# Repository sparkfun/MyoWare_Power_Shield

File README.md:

MyoWare™ Power Shield
========================================

[*MyoWare™ Power Shield (DEV-13684)*](https://www.sparkfun.com/products/13684)

The MyoWare™ Power Shield is designed to pair with the MyoWare™ Muscle Sensor.  It provides power to the muscle sensor in the form of 2 x 20mm coin cells ([CR2032](https://www.sparkfun.com/products/338), [CR2025](https://www.sparkfun.com/products/11928), LR2032, etc).

Repository Contents
-------------------

* **/Hardware** - Eagle design files (.brd, .sch)
* **/Production** - Production panel files (.brd)

Documentation
--------------
* **[Hookup Guide](https://learn.sparkfun.com/tutorials/myoware-muscle-sensor-kit)** - Basic hookup guide for the MyoWare™ Power Shield.

Product Versions
----------------
* [v1.0](https://www.sparkfun.com/products/13684)- MyoWare™ Power Shield

License Information
-------------------

This product is _**open source**_!

Please review the LICENSE.md file for license information.

If you have any questions or concerns on licensing, please contact techsupport@sparkfun.com.

Distributed as-is; no warranty is given.

- Your friends at SparkFun.

Designed by Brian E. Kaminski of Advancer Technologies

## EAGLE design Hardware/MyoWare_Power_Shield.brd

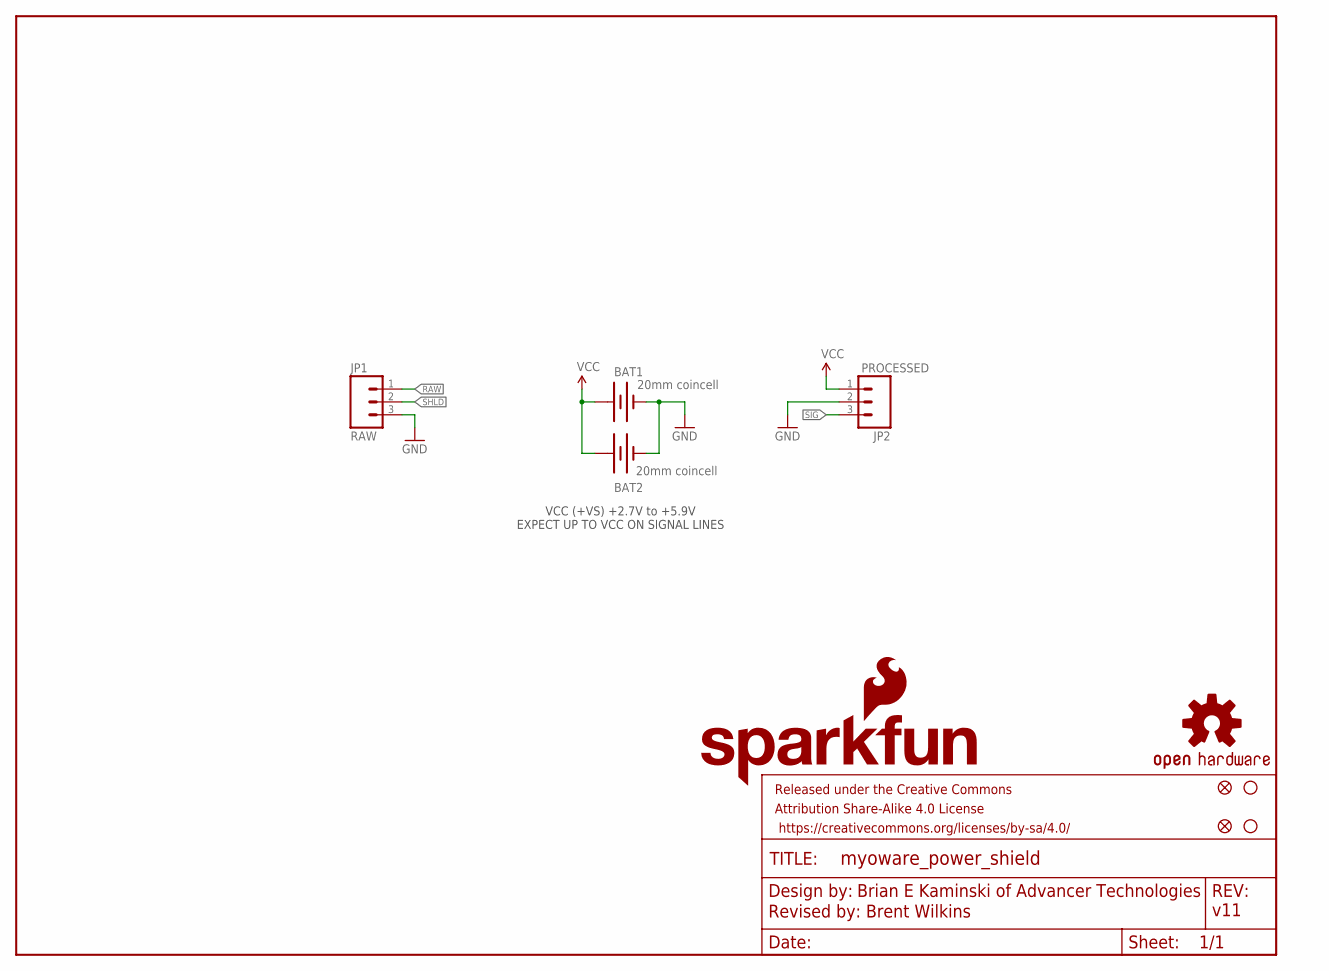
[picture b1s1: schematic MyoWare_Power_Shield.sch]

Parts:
BAT1, BAT2: 20mm coincell; BATTCON_20MM_4LEGS
FID1, FID2: FIDUCIAL1X2; FIDUCIAL-1X2
FRAME1: FRAME-LETTER; CREATIVE_COMMONS
JP1: RAW; 1X03_NO_SILK
JP2: PROCESSED; 1X03_NO_SILK
JP3, JP4: STAND-OFF
LOGO1: SFE_LOGO_NAME_FLAME.1_INCH; SFE_LOGO_NAME_FLAME_.1
LOGO2: OSHW-LOGOM; OSHW-LOGO-M

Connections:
GND: BAT1.2 (-), BAT2.2 (-), JP1.3 (1), JP2.2
RAW: JP1.1 (3)
SHLD: JP1.2
SIG: JP2.3
VCC: BAT1.1 (+), BAT2.1 (+), JP2.1

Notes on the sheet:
Brian E Kaminski of Advancer Technologies
Revised by: Brent Wilkins
v11
VCC (+VS) +2.7V to +5.9V EXPECT UP TO VCC ON SIGNAL LINES

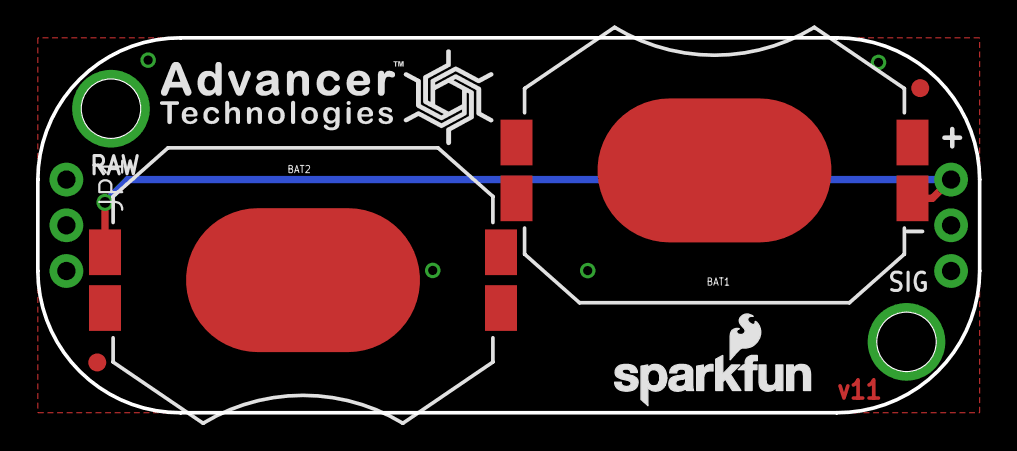
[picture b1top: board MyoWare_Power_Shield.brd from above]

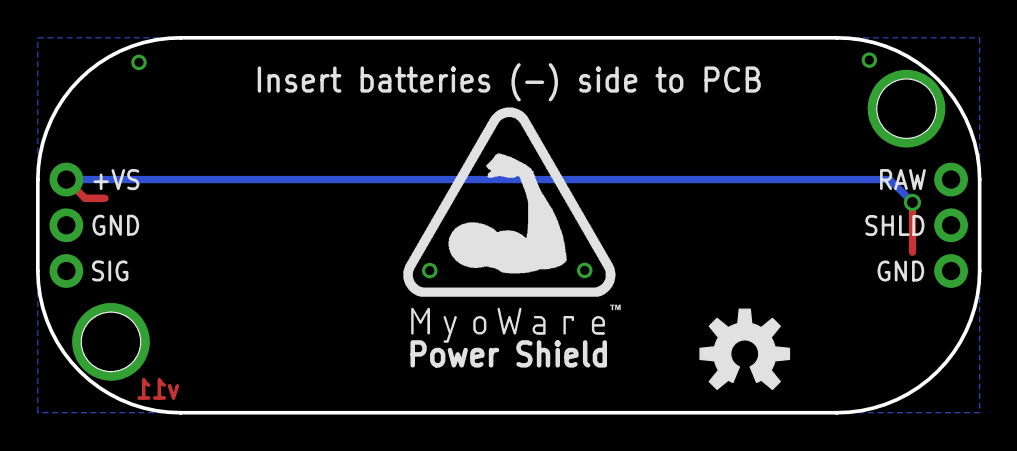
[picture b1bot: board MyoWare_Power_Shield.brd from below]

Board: 2 copper layers, 52.3 x 20.8 mm, 14 parts (2 on the bottom side), 2 nets.

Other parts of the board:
U$1: MYOWARE_LOGO
U$2: ADVANCER_LOGO
U$9: SPIRAL_LOGO_60%

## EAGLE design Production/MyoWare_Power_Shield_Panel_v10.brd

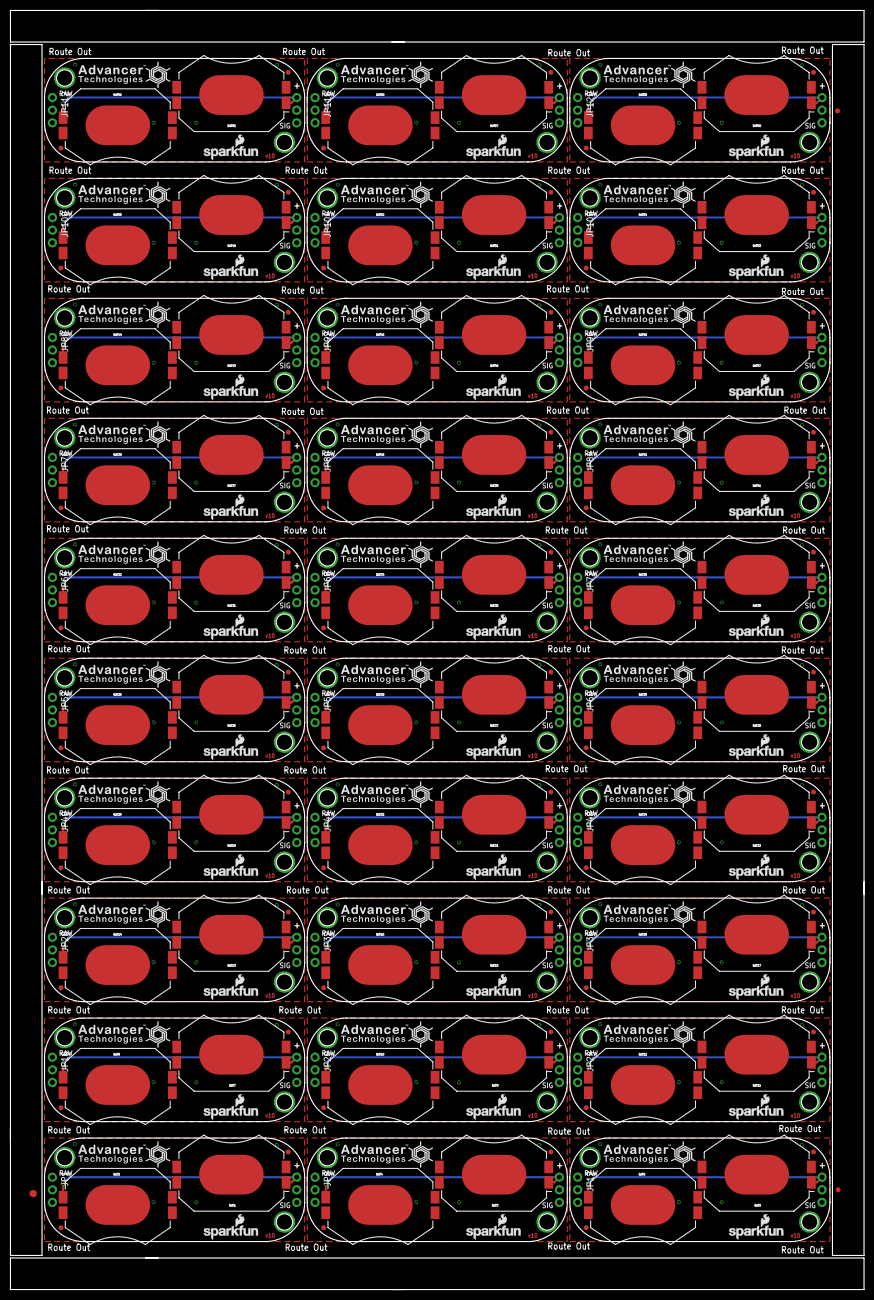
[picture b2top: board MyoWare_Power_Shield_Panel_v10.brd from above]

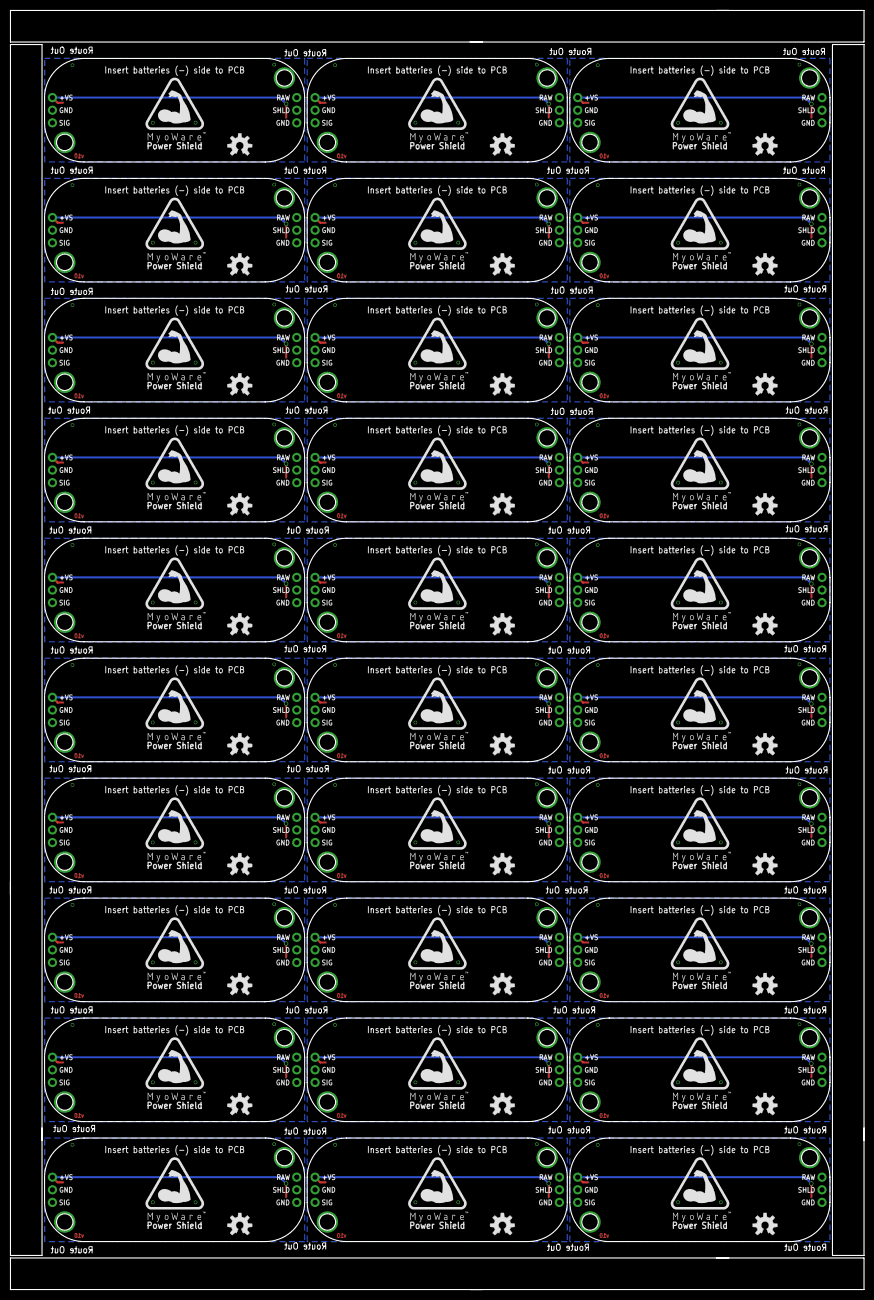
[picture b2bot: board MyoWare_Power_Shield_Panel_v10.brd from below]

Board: 2 copper layers, 171.7 x 257.3 mm, 393 parts (60 on the bottom side), 60 nets.

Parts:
BAT1, BAT2, BAT3, BAT4, BAT5, BAT6, BAT7, BAT8, BAT9, BAT10, BAT11, BAT12, BAT13, BAT14, BAT15, BAT16, BAT17, BAT18, BAT19, BAT20, BAT21, BAT22, BAT23, BAT24, BAT25, BAT26, BAT27, BAT28, BAT29, BAT30, BAT31, BAT32, BAT33, BAT34, BAT35, BAT36, BAT37, BAT38, BAT39, BAT40, BAT41, BAT42, BAT43, BAT44, BAT45, BAT46, BAT47, BAT48, BAT49, BAT50, BAT51, BAT52, BAT53, BAT54, BAT55, BAT56, BAT57, BAT58, BAT59, BAT60: 20mm coincell; BATTCON_20MM_4LEGS
E$1: FIDUCIAL-1.5X3
E$5, E$8: FIDUCIAL-1X2
FID1, FID2, FID3, FID4, FID5, FID6, FID7, FID8, FID9, FID10, FID11, FID12, FID13, FID14, FID15, FID16, FID17, FID18, FID19, FID20, FID21, FID22, FID23, FID24, FID25, FID26, FID27, FID28, FID29, FID30, FID31, FID32, FID33, FID34, FID35, FID36, FID37, FID38, FID39, FID40, FID41, FID42, FID43, FID44, FID45, FID46, FID47, FID48, FID49, FID50, FID51, FID52, FID53, FID54, FID55, FID56, FID57, FID58, FID59, FID60: FIDUCIAL1X2; FIDUCIAL-1X2
JP1, JP8, JP12, JP16, JP20, JP24, JP28, JP32, JP36, JP40, JP44, JP48, JP52, JP56, JP60, JP64, JP68, JP72, JP76, JP80, JP84, JP88, JP92, JP96, JP100, JP104, JP108, JP112, JP116, JP120: RAW; 1X03_NO_SILK
JP2, JP5, JP9, JP13, JP17, JP21, JP25, JP29, JP33, JP37, JP41, JP45, JP49, JP53, JP57, JP61, JP65, JP69, JP73, JP77, JP81, JP85, JP89, JP93, JP97, JP101, JP105, JP109, JP113, JP117: PROCESSED; 1X03_NO_SILK
JP3, JP4, JP6, JP7, JP10, JP11, JP14, JP15, JP18, JP19, JP22, JP23, JP26, JP27, JP30, JP31, JP34, JP35, JP38, JP39, JP42, JP43, JP46, JP47, JP50, JP51, JP54, JP55, JP58, JP59, JP62, JP63, JP66, JP67, JP70, JP71, JP74, JP75, JP78, JP79, JP82, JP83, JP86, JP87, JP90, JP91, JP94, JP95, JP98, JP99, JP102, JP103, JP106, JP107, JP110, JP111, JP114, JP115, JP118, JP119: STAND-OFF
LOGO1, LOGO3, LOGO5, LOGO7, LOGO9, LOGO11, LOGO13, LOGO15, LOGO17, LOGO19, LOGO21, LOGO23, LOGO25, LOGO27, LOGO29, LOGO31, LOGO33, LOGO35, LOGO37, LOGO39, LOGO41, LOGO43, LOGO45, LOGO47, LOGO49, LOGO51, LOGO53, LOGO55, LOGO57, LOGO59: SFE_LOGO_NAME_FLAME.1_INCH; SFE_LOGO_NAME_FLAME_.1
LOGO2, LOGO4, LOGO6, LOGO8, LOGO10, LOGO12, LOGO14, LOGO16, LOGO18, LOGO20, LOGO22, LOGO24, LOGO26, LOGO28, LOGO30, LOGO32, LOGO34, LOGO36, LOGO38, LOGO40, LOGO42, LOGO44, LOGO46, LOGO48, LOGO50, LOGO52, LOGO54, LOGO56, LOGO58, LOGO60: OSHW-LOGOM; OSHW-LOGO-M
U$1, U$5, U$8, U$12, U$15, U$18, U$21, U$24, U$27, U$30, U$33, U$36, U$39, U$42, U$45, U$48, U$51, U$54, U$57, U$60, U$63, U$66, U$69, U$72, U$75, U$78, U$81, U$84, U$87, U$90: MYOWARE_LOGO
U$2, U$4, U$7, U$11, U$14, U$17, U$20, U$23, U$26, U$29, U$32, U$35, U$38, U$41, U$44, U$47, U$50, U$53, U$56, U$59, U$62, U$65, U$68, U$71, U$74, U$77, U$80, U$83, U$86, U$89: ADVANCER_LOGO
U$3, U$6, U$9, U$10, U$13, U$16, U$19, U$22, U$25, U$28, U$31, U$34, U$37, U$40, U$43, U$46, U$49, U$52, U$55, U$58, U$61, U$64, U$67, U$70, U$73, U$76, U$79, U$82, U$85, U$88: SPIRAL_LOGO_60%

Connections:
GND: BAT1.2, BAT2.2, JP1.3, JP2.2
GND1: BAT3.2, BAT4.2, JP5.2, JP8.3
GND2: BAT5.2, BAT6.2, JP9.2, JP12.3
GND3: BAT7.2, BAT8.2, JP13.2, JP16.3
GND4: BAT9.2, BAT10.2, JP17.2, JP20.3
GND5: BAT11.2, BAT12.2, JP21.2, JP24.3
GND6: BAT13.2, BAT14.2, JP25.2, JP28.3
GND7: BAT15.2, BAT16.2, JP29.2, JP32.3
GND8: BAT17.2, BAT18.2, JP33.2, JP36.3
GND9: BAT19.2, BAT20.2, JP37.2, JP40.3
GND10: BAT21.2, BAT22.2, JP41.2, JP44.3
GND11: BAT23.2, BAT24.2, JP45.2, JP48.3
GND12: BAT25.2, BAT26.2, JP49.2, JP52.3
GND13: BAT27.2, BAT28.2, JP53.2, JP56.3
GND14: BAT29.2, BAT30.2, JP57.2, JP60.3
GND15: BAT31.2, BAT32.2, JP61.2, JP64.3
GND16: BAT33.2, BAT34.2, JP65.2, JP68.3
GND17: BAT35.2, BAT36.2, JP69.2, JP72.3
GND18: BAT37.2, BAT38.2, JP73.2, JP76.3
GND19: BAT39.2, BAT40.2, JP77.2, JP80.3
GND20: BAT41.2, BAT42.2, JP81.2, JP84.3
GND21: BAT43.2, BAT44.2, JP85.2, JP88.3
GND22: BAT45.2, BAT46.2, JP89.2, JP92.3
GND23: BAT47.2, BAT48.2, JP93.2, JP96.3
GND24: BAT49.2, BAT50.2, JP97.2, JP100.3
GND25: BAT51.2, BAT52.2, JP101.2, JP104.3
GND26: BAT53.2, BAT54.2, JP105.2, JP108.3
GND27: BAT55.2, BAT56.2, JP109.2, JP112.3
GND28: BAT57.2, BAT58.2, JP113.2, JP116.3
GND29: BAT59.2, BAT60.2, JP117.2, JP120.3
VCC: BAT1.1, BAT2.1, JP2.1
VCC1: BAT3.1, BAT4.1, JP5.1
VCC2: BAT5.1, BAT6.1, JP9.1
VCC3: BAT7.1, BAT8.1, JP13.1
VCC4: BAT9.1, BAT10.1, JP17.1
VCC5: BAT11.1, BAT12.1, JP21.1
VCC6: BAT13.1, BAT14.1, JP25.1
VCC7: BAT15.1, BAT16.1, JP29.1
VCC8: BAT17.1, BAT18.1, JP33.1
VCC9: BAT19.1, BAT20.1, JP37.1
VCC10: BAT21.1, BAT22.1, JP41.1
VCC11: BAT23.1, BAT24.1, JP45.1
VCC12: BAT25.1, BAT26.1, JP49.1
VCC13: BAT27.1, BAT28.1, JP53.1
VCC14: BAT29.1, BAT30.1, JP57.1
VCC15: BAT31.1, BAT32.1, JP61.1
VCC16: BAT33.1, BAT34.1, JP65.1
VCC17: BAT35.1, BAT36.1, JP69.1
VCC18: BAT37.1, BAT38.1, JP73.1
VCC19: BAT39.1, BAT40.1, JP77.1
VCC20: BAT41.1, BAT42.1, JP81.1
VCC21: BAT43.1, BAT44.1, JP85.1
VCC22: BAT45.1, BAT46.1, JP89.1
VCC23: BAT47.1, BAT48.1, JP93.1
VCC24: BAT49.1, BAT50.1, JP97.1
VCC25: BAT51.1, BAT52.1, JP101.1
VCC26: BAT53.1, BAT54.1, JP105.1
VCC27: BAT55.1, BAT56.1, JP109.1
VCC28: BAT57.1, BAT58.1, JP113.1
VCC29: BAT59.1, BAT60.1, JP117.1

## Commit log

2015-07-09 Tweaks to bring up to checklist standards
2015-07-10 Moved power trace to back
2015-07-21 Moved fiducials & removed a tiny dimension layer artifact
2015-07-24 moved position of labeled net in schematic
2015-08-31 Changed to standard paste version of battery holder
2015-09-21 Removed RoHS claim & bumped to v10
2015-09-21 Removed missed merge conflict
2015-09-22 Expanded dimensions to nearest 0.01" grid
2015-10-15 Unhid possible airwires on GND signal
2015-10-15 created panel v10
2016-02-17 Updated DRC to 25mil mask limit to tent via

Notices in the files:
parts and their libraries:
SparkFunJan2012: Licensing: CC v3.0 Share-Alike You are welcome to use this library for commercial purposes.
SparkFun-Aesthetics: Licensing: Creative Commons ShareAlike 4.0 International - https://creativecommons.org/licenses/by-sa/4.0
SparkFun-Aesthetics: Released under the Creative Commons
